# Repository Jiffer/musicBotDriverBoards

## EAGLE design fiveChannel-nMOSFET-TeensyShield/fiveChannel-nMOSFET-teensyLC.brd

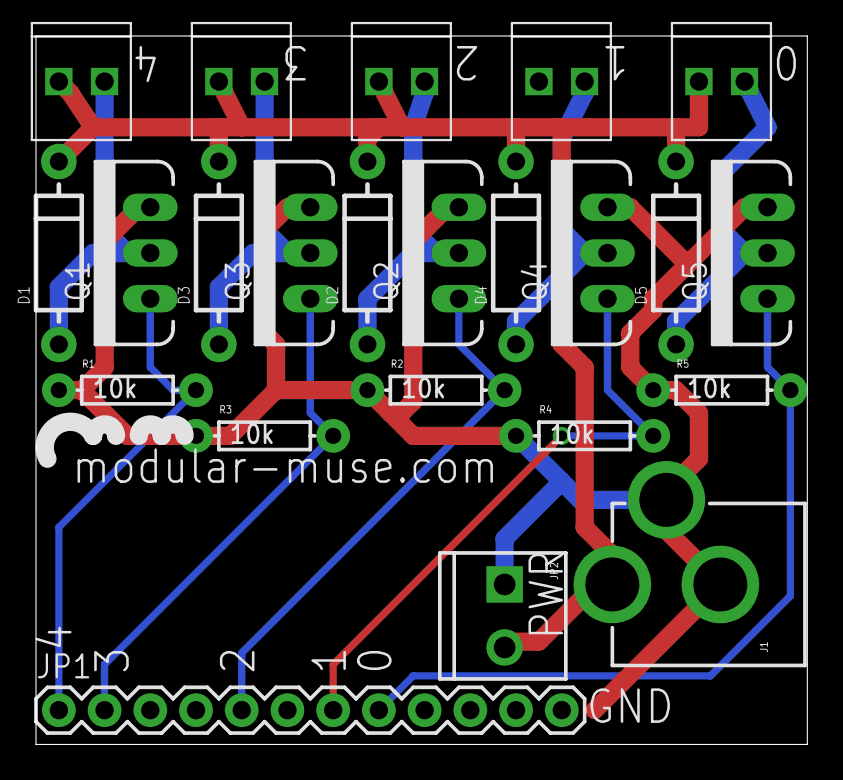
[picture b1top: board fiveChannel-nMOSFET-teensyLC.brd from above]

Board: 2 copper layers, 42.9 x 39.4 mm, 23 parts (0 on the bottom side), 12 nets.

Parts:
D1, D2, D3, D4, D5: DIODE-1N4001
J1: POWER_JACKPTH; POWER_JACK_PTH
JP1: M12PTH; 1X12
JP2: M023.5MM; SCREWTERMINAL-3.5MM-2
JP3, JP4, JP5, JP9, JP10: M022.54MM_SCREWTERM; 1X02_2.54_SCREWTERM
Q1, Q2, Q3, Q4, Q5: TO220V
R1, R2, R3, R4, R5: 10k; AXIAL-0.3

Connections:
0: JP1.1, Q1.1, R1.P$2
1: JP1.2, Q3.1, R3.P$2
2: JP1.5, Q2.1, R2.P$2
3: JP1.7, Q4.1, R4.P$2
4: JP1.8, Q5.1, R5.P$2
D0: D1.A, JP3.P1, Q1.2
D1: D3.A, JP4.P1, Q3.2
D2: D2.A, JP10.P1, Q2.2
D3: D4.A, JP9.P1, Q4.2
D4: D5.A, JP5.P1, Q5.2
GND: J1.GND, J1.GNDBREAK, JP1.12, JP2.1, Q1.3, Q2.3, Q3.3, Q4.3, Q5.3, R1.P$1, R2.P$1, R3.P$1, R4.P$1, R5.P$1
POWER: D1.C, D2.C, D3.C, D4.C, D5.C, J1.PWR, JP2.2, JP3.P2, JP4.P2, JP5.P2, JP9.P2, JP10.P2

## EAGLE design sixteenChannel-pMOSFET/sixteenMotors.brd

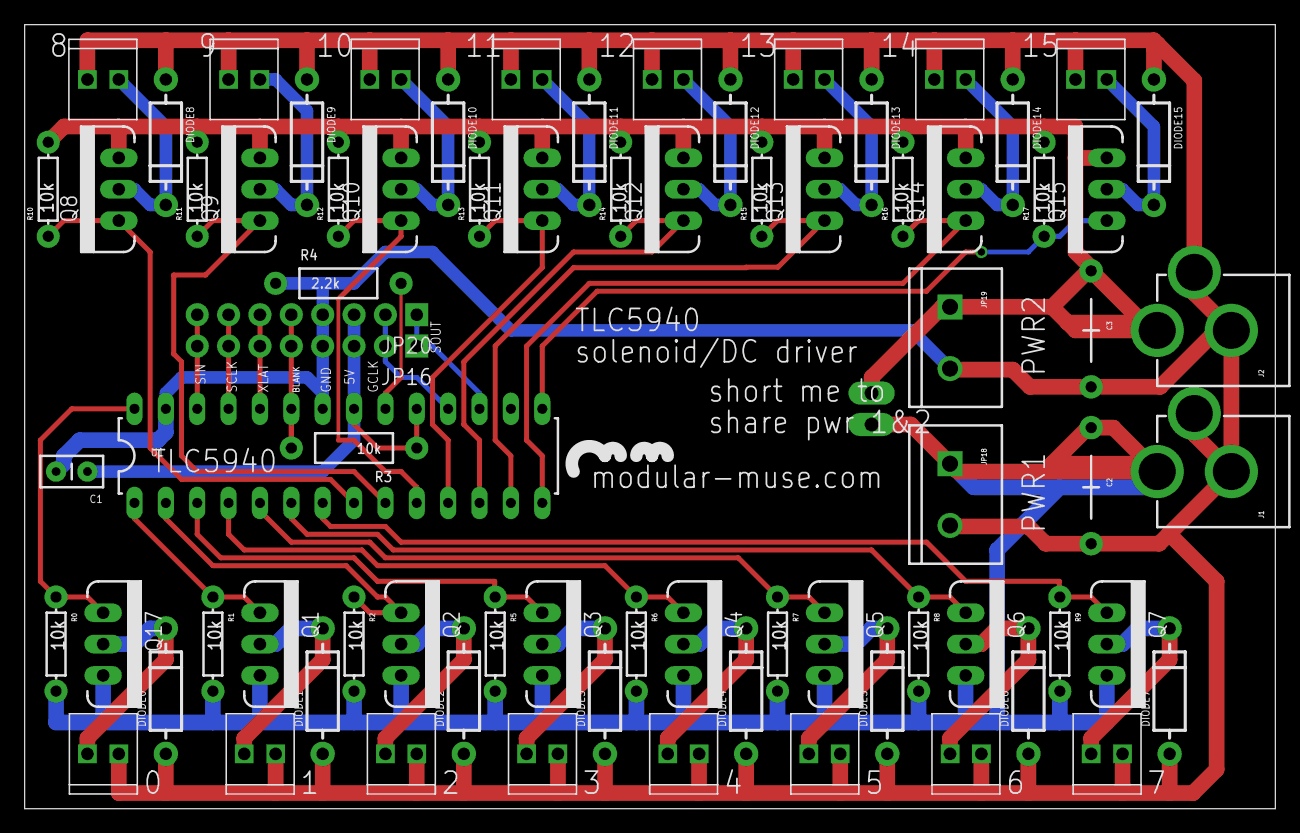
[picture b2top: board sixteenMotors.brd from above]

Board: 2 copper layers, 101.3 x 63.5 mm, 77 parts (0 on the bottom side), 43 nets.

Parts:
C1: CAP-PTH-SMALLEZ
C2, C3: CAP-PTH-LARGE
DIODE0, DIODE1, DIODE2, DIODE3, DIODE4, DIODE5, DIODE6, DIODE7, DIODE8, DIODE9, DIODE10, DIODE11, DIODE12, DIODE13, DIODE14, DIODE15: DIODE-1N4001
J1, J2: POWER_JACKPTH; POWER_JACK_PTH
JP1, JP2, JP3, JP4, JP5, JP6, JP7, JP8, JP9, JP10, JP11, JP12, JP13, JP14, JP15, JP17: M022.54MM_SCREWTERM; 1X02_2.54_SCREWTERM
JP16, JP20: 1X08_PIN1_NO_SILK
JP18, JP19: M025MM; SCREWTERMINAL-5MM-2
JP21: M02PTH3; 1X02_LONGPADS
Q1, Q2, Q3, Q4, Q5, Q6, Q7, Q8, Q9, Q10, Q11, Q12, Q13, Q14, Q15, Q17: MOSFET-PCHANNELFQP27P06; TO220V
R0, R1, R2, R5, R6, R7, R8, R9, R10, R11, R12, R13, R14, R15, R16, R17: 10k; AXIAL-0.3
R3: 10k; AXIAL-0.4
R4: 2.2k; AXIAL-0.4
U1: TLC5940-NT; DIL28-3

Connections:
BLANK: JP16.5, JP20.5, R3.P$2, U1.23
DRAIN0: DIODE0.C, JP17.P1, Q17.2
DRAIN1: DIODE1.C, JP1.P1, Q1.2
DRAIN2: DIODE2.C, JP2.P1, Q2.2
DRAIN3: DIODE3.C, JP3.P1, Q3.2
DRAIN4: DIODE4.C, JP4.P1, Q4.2
DRAIN5: DIODE5.C, JP5.P1, Q5.2
DRAIN6: DIODE6.C, JP6.P1, Q6.2
DRAIN7: DIODE7.C, JP7.P1, Q7.2
DRAIN8: DIODE8.C, JP8.P1, Q8.2
DRAIN9: DIODE9.C, JP9.P1, Q9.2
DRAIN10: DIODE10.C, JP10.P1, Q10.2
DRAIN11: DIODE11.C, JP11.P1, Q11.2
DRAIN12: DIODE12.C, JP12.P1, Q12.2
DRAIN13: DIODE13.C, JP13.P1, Q13.2
DRAIN14: DIODE14.C, JP14.P1, Q14.2
DRAIN15: DIODE15.C, JP15.P1, Q15.2
GND: C1.2, C2.2, C3.2, DIODE0.A, DIODE1.A, DIODE2.A, DIODE3.A, DIODE4.A, DIODE5.A, DIODE6.A, DIODE7.A, DIODE8.A, DIODE9.A, DIODE10.A, DIODE11.A, DIODE12.A, DIODE13.A, DIODE14.A, DIODE15.A, J1.GND, J1.GNDBREAK, J2.GND, J2.GNDBREAK, JP1.P2, JP2.P2, JP3.P2, JP4.P2, JP5.P2, JP6.P2, JP7.P2, JP8.P2, JP9.P2, JP10.P2, JP11.P2, JP12.P2, JP13.P2, JP14.P2, JP15.P2, JP16.4, JP17.P2, JP18.2, JP19.2, JP20.4, R4.P$1, U1.22, U1.27
GSCLK: JP16.2, JP20.2, U1.18
unnamed: R4.P$2, U1.20
O0: Q17.1, R0.P$1, U1.28
O1: Q1.1, R1.P$1, U1.1
O2: Q2.1, R2.P$1, U1.2
O3: Q3.1, R5.P$1, U1.3
O4: Q4.1, R6.P$1, U1.4
O5: Q5.1, R7.P$1, U1.5
O6: Q6.1, R8.P$1, U1.6
O7: Q7.1, R9.P$1, U1.7
O8: Q8.1, R10.P$1, U1.8
O9: Q9.1, R11.P$1, U1.9
O10: Q10.1, R12.P$1, U1.10
O11: Q11.1, R13.P$1, U1.11
O12: Q12.1, R14.P$1, U1.12
O13: Q13.1, R15.P$1, U1.13
O14: Q14.1, R16.P$1, U1.14
O15: Q15.1, R17.P$1, U1.15
POWER1: C2.1, J1.PWR, JP18.1, JP21.2, Q1.3, Q2.3, Q3.3, Q4.3, Q5.3, Q6.3, Q7.3, Q17.3, R0.P$2, R1.P$2, R2.P$2, R5.P$2, R6.P$2, R7.P$2, R8.P$2, R9.P$2
POWER2: C3.1, J2.PWR, JP19.1, JP21.1, Q8.3, Q9.3, Q10.3, Q11.3, Q12.3, Q13.3, Q14.3, Q15.3, R10.P$2, R11.P$2, R12.P$2, R13.P$2, R14.P$2, R15.P$2, R16.P$2, R17.P$2
SCLK: JP16.7, JP20.7, U1.25
SIN: JP16.8, JP20.8, U1.26
SOUT: JP16.1, JP20.1, U1.17
VCC: C1.1, JP16.3, JP20.3, R3.P$1, U1.19, U1.21
XLAT: JP16.6, JP20.6, U1.24

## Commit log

2016-10-19 initial upload of Eagle files for 3 motor driver boards

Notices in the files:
parts and their libraries:
SparkFun-DiscreteSemi: Licensing: Creative Commons ShareAlike 4.0 International - https://creativecommons.org/licenses/by-sa/4.0
